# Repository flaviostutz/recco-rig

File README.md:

# recco-rig
This is a board to help musicians perform recordings along with Recco App.

## Board

The board schematics was created using the free version of Eagle.

To install it, go to https://www.autodesk.com/products/eagle/free-download

### Top

### Bottom

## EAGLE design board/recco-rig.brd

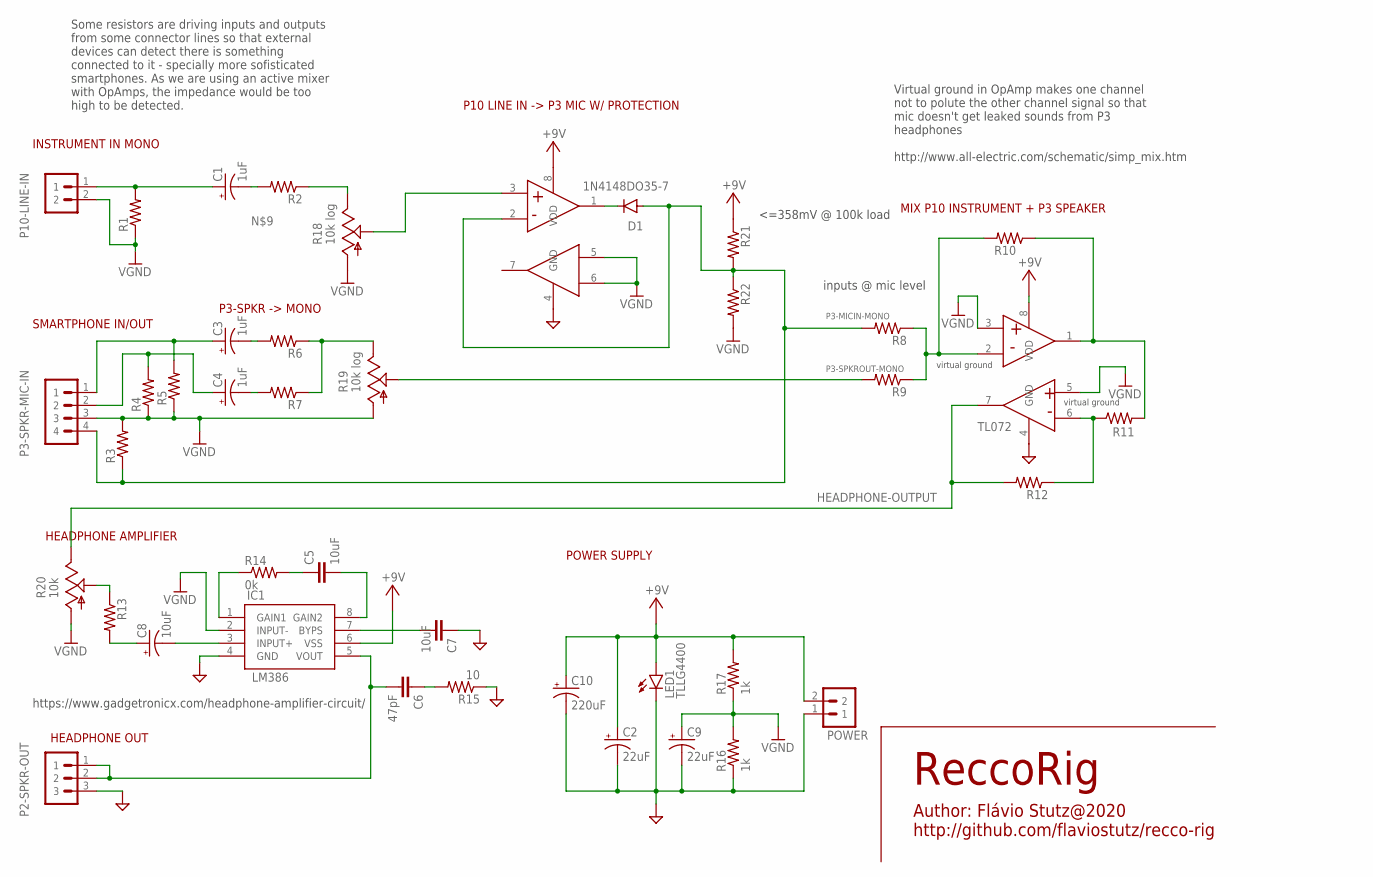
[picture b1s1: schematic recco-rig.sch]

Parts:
C1, C3, C4: 1uF; E2,5-6E
C2, C9: 22uF; E2,5-6E
C5, C7: 10uF; C050-024X044
C6: 47pF; C050-024X044
C8: 10uF; E2,5-6E
C10: 220uF; E2,5-6E
D1: 1N4148DO35-7; DO35-7
IC1: LM386; PDIP-8PIN
IC2: TL072-OPAMP; PDIP-8PIN
LED1: TLLG4400; LED3MM
P2-SPKR-OUT: PIN-HEADER-3PIN
P3-SPKR-MIC-IN: PIN-HEADER-4PIN
P10-LINE-IN: PIN-HEADER-2PIN
POWER: PIN-HEADER-2PIN
R1, R8, R9, R10, R11, R12, R21: 10k; RESISTOR-V1
R2, R6, R7: 300; RESISTOR-V1
R3, R4, R5, R22: 1k; RESISTOR-V1
R13: 100; RESISTOR-V1
R14: 0k; 0309V
R15: 10; 0309V
R16, R17: 1k; 0309V
R18, R19: 10k log; B25U
R20: 10k; B25U
U$12: TL072-OPAMP; PDIP-8PIN

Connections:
+9V: C2.+, C10.+, IC1.6 (VSS), IC2.8 (VDD), LED1.A, POWER.2, R17.2, R21.1, U$12.8 (VDD)
GND: C2.-, C7.1, C9.-, C10.-, IC1.4 (GND), IC2.4 (GND), LED1.K (C), P2-SPKR-OUT.3, POWER.1, R15.1, R16.1, U$12.4 (GND)
HEADPHONE-OUTPUT: IC2.7 (2OUT), R12.2, R20.E
unnamed: C1.-, R2.2
unnamed: C3.-, R6.2
unnamed: C4.-, R7.2
unnamed: IC2.2 (1IN-), R8.1, R9.1, R10.2
unnamed: IC2.1 (1OUT), R10.1, R11.2
unnamed: IC2.6 (2IN-), R11.1, R12.1
unnamed: C6.1, R15.2
unnamed: C3.+, P3-SPKR-MIC-IN.1, R5.2
unnamed: R2.1, R18.E
unnamed: C8.+, R13.2
unnamed: R13.1, R20.S
unnamed: C5.2, IC1.8 (GAIN2)
unnamed: C5.1, R14.2
unnamed: IC1.1 (GAIN1), R14.1
unnamed: C6.2, IC1.5 (VOUT), P2-SPKR-OUT.1, P2-SPKR-OUT.2
unnamed: C7.2, IC1.7 (BYPS)
unnamed: C8.-, IC1.3 (INPUT+)
unnamed: R6.1, R7.1, R19.E
unnamed: R18.S, U$12.3 (1IN+)
unnamed: D1.C, U$12.1 (1OUT)
P3-MICIN-MONO: D1.A, P3-SPKR-MIC-IN.4, R3.1, R8.2, R21.2, R22.1, U$12.2 (1IN-)
P3-SPKROUT-MONO: R9.2, R19.S
P3-SPKROUT-R: C4.+, P3-SPKR-MIC-IN.2, R4.2
P10-LINEIN-MONO: C1.+, P10-LINE-IN.1, R1.2
VGND: C9.+, IC1.2 (INPUT-), IC2.3 (1IN+), IC2.5 (2IN+), P3-SPKR-MIC-IN.3, P10-LINE-IN.2, R1.1, R3.2, R4.1, R5.1, R16.2, R17.1, R18.A, R19.A, R20.A, R22.2, U$12.5 (2IN+), U$12.6 (2IN-)

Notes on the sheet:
INSTRUMENT IN MONO
SMARTPHONE IN/OUT
HEADPHONE OUT
MIX P10 INSTRUMENT + P3 SPEAKER
Some resistors are driving inputs and outputs from some connector lines so that external devices can detect there is something connected to it - specially more sofisticated smartphones. As we are using an active mixer with OpAmps, the impedance would be too high to be detected.
P10 LINE IN -> P3 MIC W/ PROTECTION
P3-SPKR -> MONO
virtual ground
HEADPHONE AMPLIFIER
POWER SUPPLY
Virtual ground in OpAmp makes one channel not to polute the other channel signal so that mic doesn't get leaked sounds from P3 headphones http://www.all-electric.com/schematic/simp_mix.htm
TL072
Author: Flávio Stutz@2020 http://github.com/flaviostutz/recco-rig
ReccoRig
https://www.gadgetronicx.com/headphone-amplifier-circuit/
inputs @ mic level
<=358mV @ 100k load

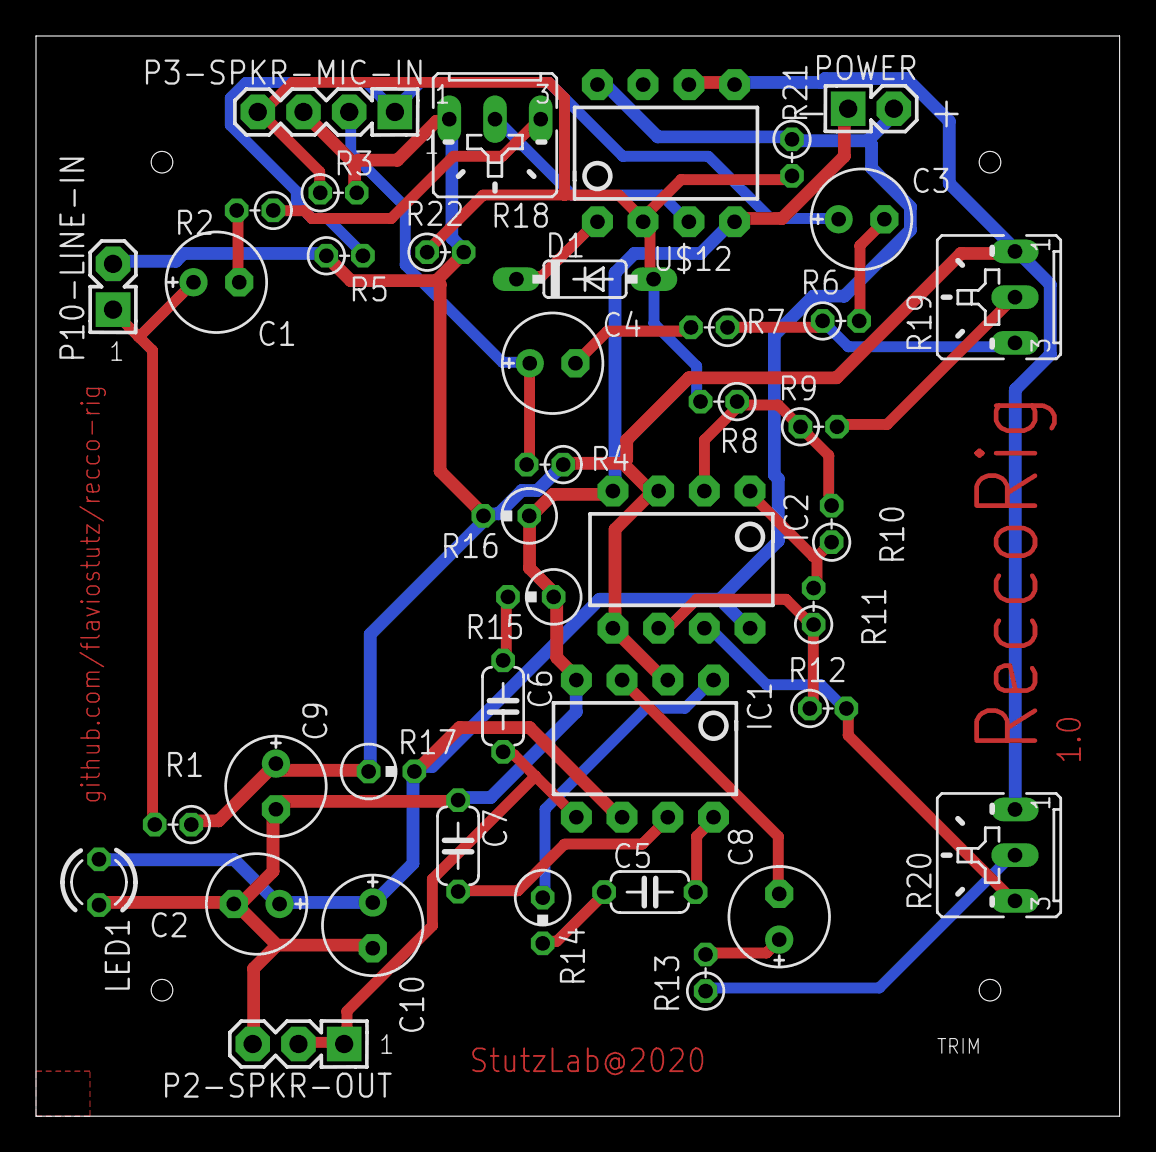
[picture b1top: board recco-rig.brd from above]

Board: 2 copper layers, 60.2 x 60.0 mm, 41 parts (0 on the bottom side), 28 nets.

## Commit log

2020-05-12 first version (no tests yet)
2020-05-12 physical boards and documentation
2020-05-13 fixing image width in readme
2020-05-13 updating readme
2020-05-17 physical board and mic protection
